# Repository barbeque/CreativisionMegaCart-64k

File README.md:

# 64K modifications
I didn't have a 27C801, so I've modified this cartridge to use a 27C512 and switch it between two 32K games.

Revised bill of materials:
 - 27c512 (E)EPROM
 - 3-pin 0.1" SPST toggle switch
 - 0.1µF disc capacitor
 - 2x 1n4148 diode

Fixed README coming soon. Original README is as follows:

# CreativisionMegaCart
NOTE: THIS IS NOT COMPATIBLE WITH THE CREATIVISION II WITHOUT MODIFICATION!
(See: http://www.madrigaldesign.it/forum/viewtopic.php?f=10&t=330&p=3201#p3201 )

Multiple ROM Cartridge system for the VTech Creativision, AKA the Dick Smith Wizzard

This is a project I’ve been working on for a while and today I’m pleased to announce the release of our open Source MultiCart system.

Clockmeister kindly gave me all the information from his cart, and gave me permission to release this as Open Source. We both also want to acknowledge and thank the great people over at the Madrigal Design Creativision forums for all their help as well.

My minor contribution was taking the design and putting it in KiCad. I had to spend a bit of time debugging, but Clockmeister assisted above and beyond the call of duty.

This design is released under a CC-BY-SA license. Remix, but always share!

I won’t include ROMs for copyright reasons but they are quite easy to locate on the net if you search around. Note: If you want to program your own EPROM, I understand you have to split the 32K image into two 16K files and then swap the first 16K with the second 16K and re-join them. Clockmeister suggests WinHEX for this.

Parts list is as follows:
1 x 27C801 EPROM (or equivalent)
1 x 0.1uF Ceramic disk capacitor
2 x 1N1418 diode (or equivalent)
1 x DIP switch block (5 switches)
1 x 6 way 4.7kΩ resistor block. (Don’t do what I did and order the 5 way because you counted the pins. It should have seven pins)

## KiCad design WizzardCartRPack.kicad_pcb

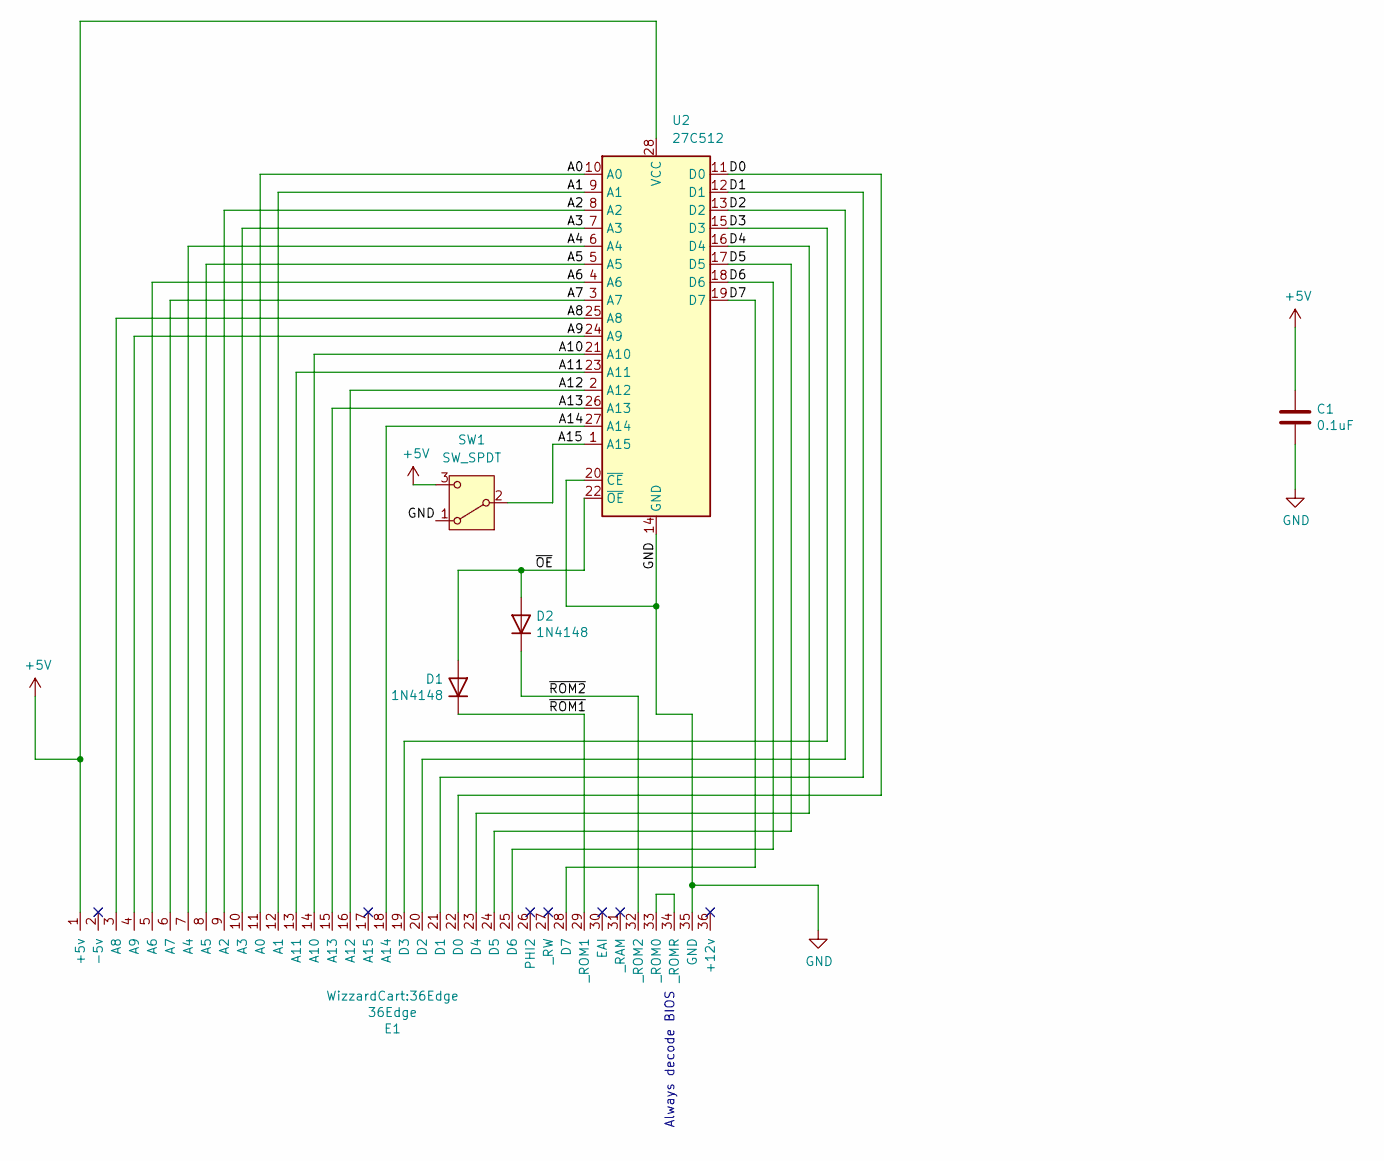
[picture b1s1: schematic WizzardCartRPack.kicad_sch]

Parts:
C1: 0.1uF; C_Disc_D8.0mm_W2.5mm_P5.00mm
D1, D2: 1N4148; D_DO-35_SOD27_P7.62mm_Horizontal
E1: 36Edge
SW1: SW_SPDT; PinHeader_1x03_P2.54mm_Vertical
U2: 27C512; DIP-28_W15.24mm

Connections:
+5V: C1.1, E1.1 (+5v), SW1.3 (C), U2.28 (VCC)
/A0: E1.11 (A0), U2.10 (A0)
/A1: E1.12 (A1), U2.9 (A1)
/A2: E1.9 (A2), U2.8 (A2)
/A3: E1.10 (A3), U2.7 (A3)
/A4: E1.7 (A4), U2.6 (A4)
/A5: E1.8 (A5), U2.5 (A5)
/A6: E1.5 (A6), U2.4 (A6)
/A7: E1.6 (A7), U2.3 (A7)
/A8: E1.3 (A8), U2.25 (A8)
/A9: E1.4 (A9), U2.24 (A9)
/A10: E1.14 (A10), U2.21 (A10)
/A11: E1.13 (A11), U2.23 (A11)
/A12: E1.16 (A12), U2.2 (A12)
/A13: E1.15 (A13), U2.26 (A13)
/A14: E1.18 (A14), U2.27 (A14)
/A15: SW1.2 (B), U2.1 (A15)
/D0: E1.22 (D0), U2.11 (D0)
/D1: E1.21 (D1), U2.12 (D1)
/D2: E1.20 (D2), U2.13 (D2)
/D3: E1.19 (D3), U2.15 (D3)
/D4: E1.23 (D4), U2.16 (D4)
/D5: E1.24 (D5), U2.17 (D5)
/D6: E1.25 (D6), U2.18 (D6)
/D7: E1.28 (D7), U2.19 (D7)
/~OE: D1.2 (A), D2.2 (A), U2.22 (~OE)
/~ROM1: D1.1 (K), E1.29 (_ROM1)
/~ROM2: D2.1 (K), E1.32 (_ROM2)
GND: C1.2, E1.35 (GND), SW1.1 (A), U2.14 (GND), U2.20 (~CE)
unnamed: E1.33 (_ROM0), E1.34 (_ROMR)

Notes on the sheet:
Always decode BIOS

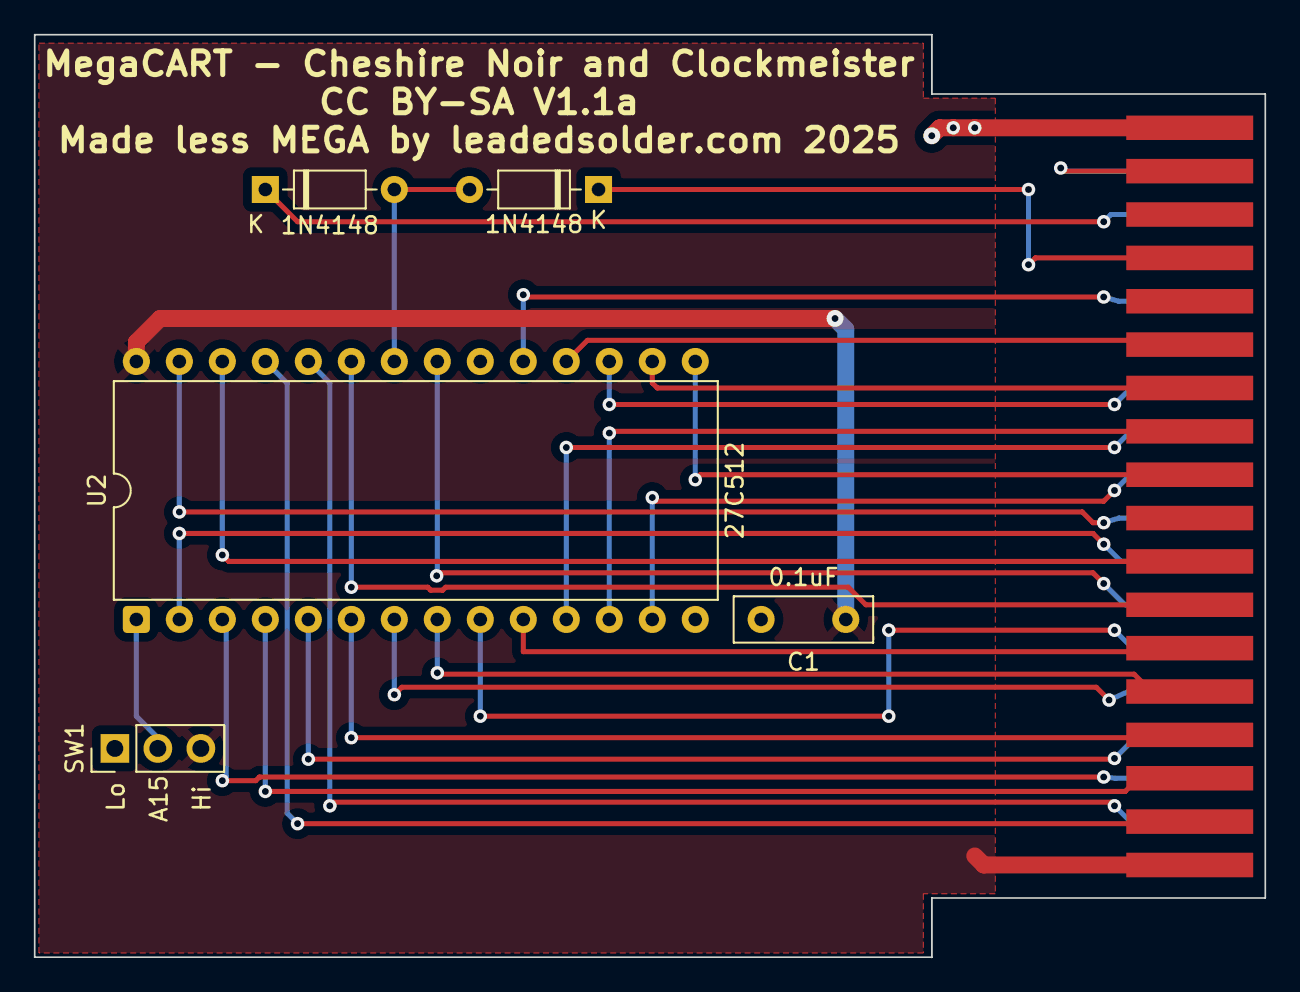
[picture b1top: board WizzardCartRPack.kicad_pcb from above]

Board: 2 copper layers, 72.7 x 54.5 mm, 6 parts (0 on the bottom side), 30 nets.

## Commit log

2025-10-03 Get rid of backup files
2025-10-03 Remove old KiCad files
2025-10-03 Update to newer KiCad
2025-10-03 Fabricated single-ROM version
2025-10-04 README
2025-10-04 TODO
2025-10-18 Move fingers up

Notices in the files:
WizzardCartRPack.kicad_pcb:
CC BY-SA V1.1a
